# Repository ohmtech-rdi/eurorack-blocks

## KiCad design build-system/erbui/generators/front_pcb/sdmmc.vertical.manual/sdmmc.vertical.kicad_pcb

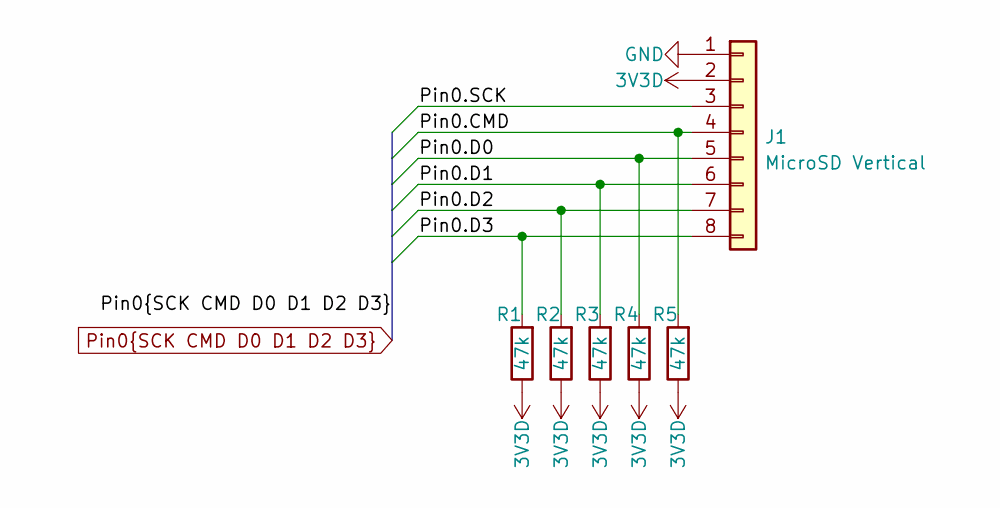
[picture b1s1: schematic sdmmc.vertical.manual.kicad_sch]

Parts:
J1: MicroSD Vertical; VERT_MICROSD_CENTERED; MPN PJS008U-3000-0
R1, R2, R3, R4, R5: 47k; R_0603_1608Metric; MPN RC0603JR-0747KL; JlcPcbPlace Yes

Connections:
3V3D: J1.2, R1.1, R2.1, R3.1, R4.1, R5.1
GND: J1.1
Pin0.CMD: J1.4, R5.2
Pin0.D0: J1.5, R4.2
Pin0.D1: J1.6, R3.2
Pin0.D2: J1.7, R2.2
Pin0.D3: J1.8, R1.2
Pin0.SCK: J1.3

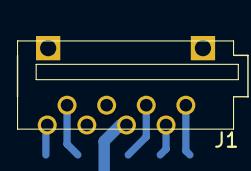
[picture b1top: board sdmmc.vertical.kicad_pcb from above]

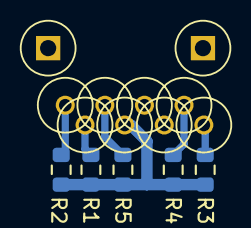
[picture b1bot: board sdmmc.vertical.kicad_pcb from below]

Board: 2 copper layers, 6 parts (5 on the bottom side), 6 nets.
